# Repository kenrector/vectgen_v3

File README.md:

# vectgen_v3
kicad project for Wells-Gardner display controller

This is an ESP32 based interface to the Wells-Gardner 15v2000 BW X-Y display perhaps originally found
in the Atari Asteroids and Lunar Lander cocktail style arcade games.  The display is controlled by
X-Y voltages in the ranges +/- 0-10v and Z voltage 0-5v. 

The ESP32 processor is resident on a Wiretag WT32-ETH01 board and interfaces with client software via
the LAN connection.

Input commands from the client are move, draw, and zero, with related 12bit vector values sent to
X and Y MCP4922 DAC channels via the SPI interface.

Output from the DAC is translated to a bipolar voltage input to op amp integrator.  Integrator output is
input to the WG display.

Integrator input is switched by ADG201S CMOS switches controlled by the ESP32 software.  The integrators
are reset to zero by ADG201s switches also controlled by the ESP32.

A Z axis control to switch the CRT beam is provided by simple transistor logic.

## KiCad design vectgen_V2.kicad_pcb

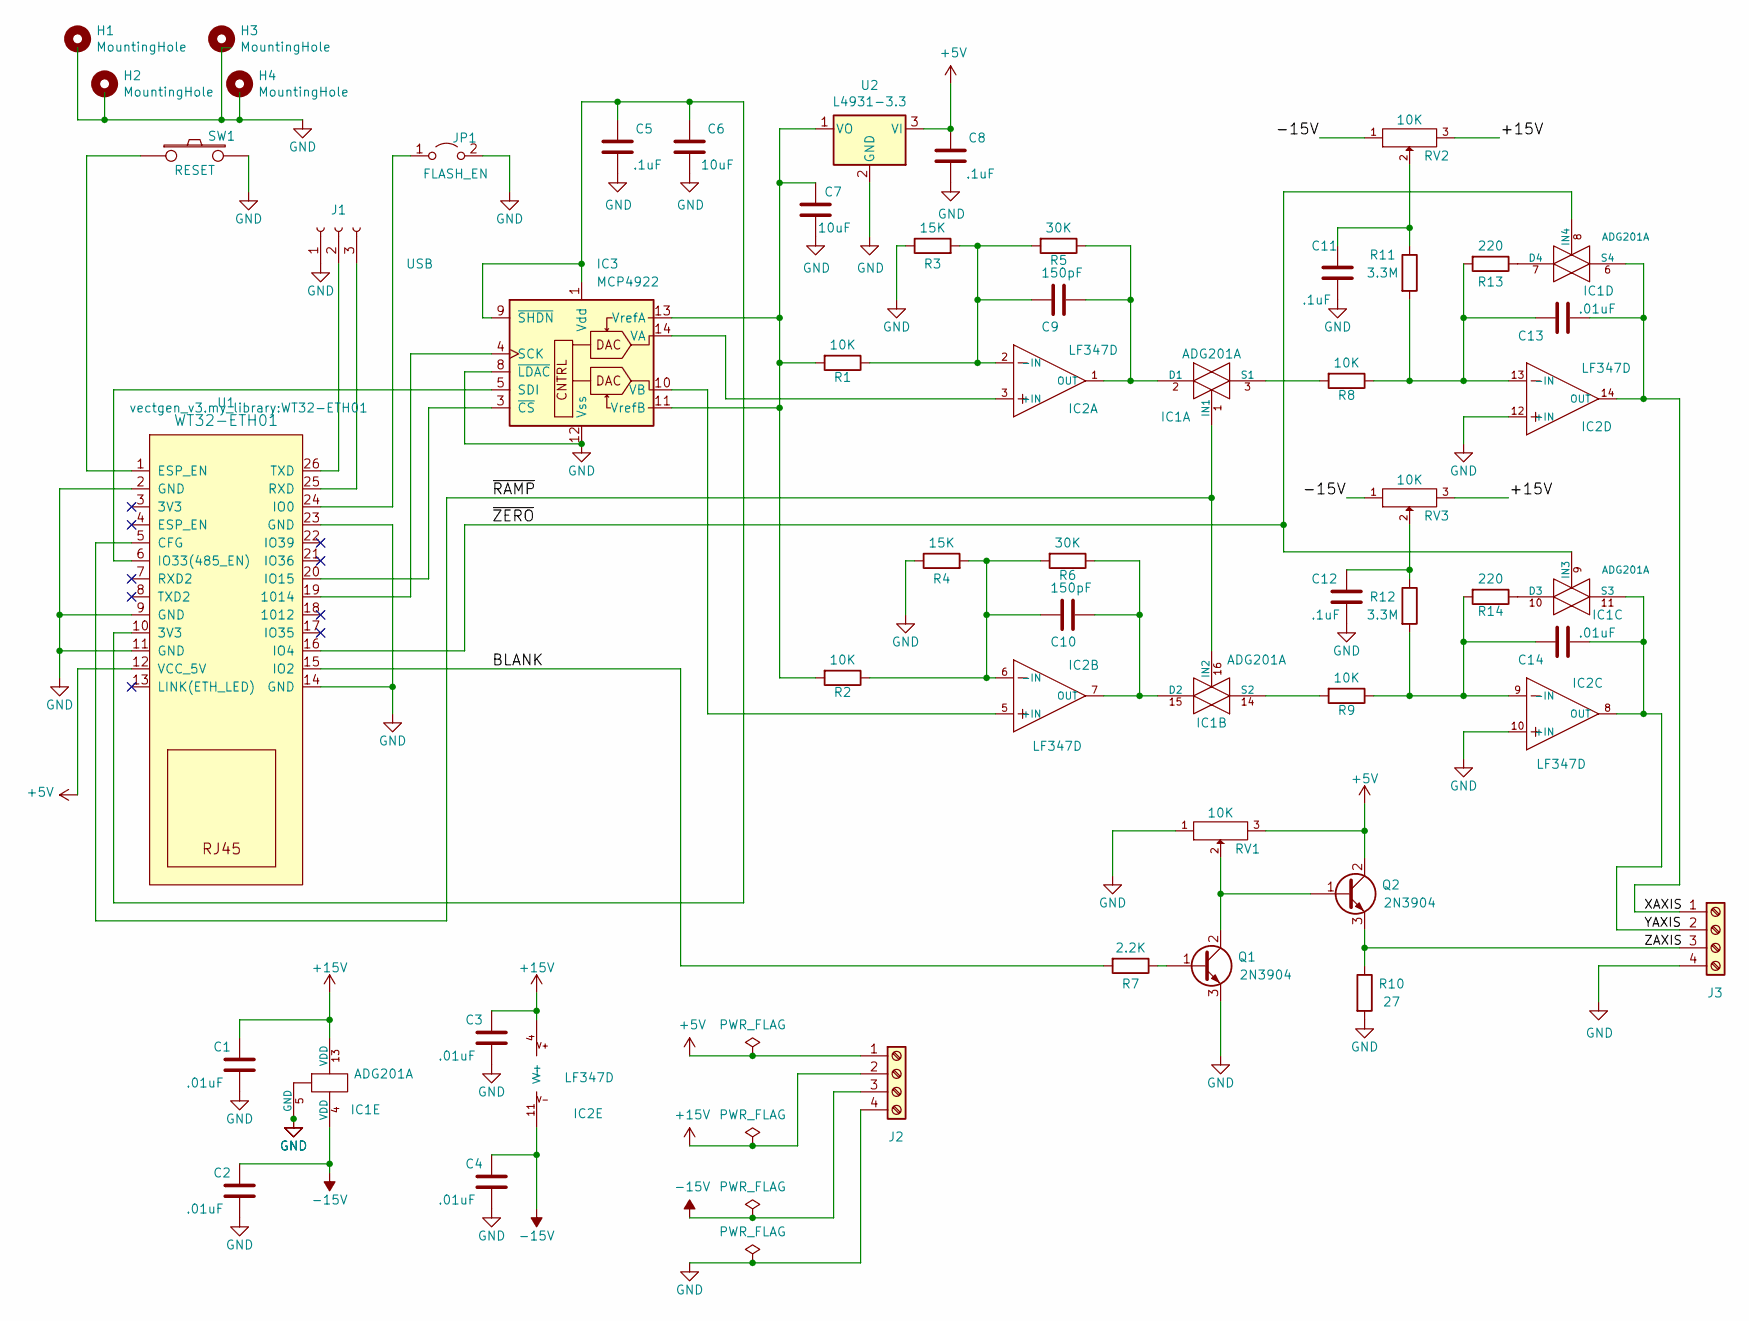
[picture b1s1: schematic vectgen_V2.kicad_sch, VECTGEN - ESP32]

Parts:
C1, C2, C3, C4: .01uF; C_Disc_D5.0mm_W2.5mm_P5.00mm
C5, C8, C11, C12: .1uF; C_Disc_D5.0mm_W2.5mm_P5.00mm
C6, C7: 10uF; C_Disc_D5.0mm_W2.5mm_P5.00mm
C9, C10: 150pF; C_Disc_D5.0mm_W2.5mm_P5.00mm
C13, C14: .01uF; C_Rect_L11.0mm_W2.8mm_P10.00mm_MKT
H1, H2, H3, H4: MountingHole; MountingHole_3.7mm_Pad_TopBottom
IC1: ADG201A; DIP-16_W7.62mm
IC2: LF347D; DIP-14_W7.62mm
IC3: MCP4922; DIP-14_W7.62mm
J1: USB; PinHeader_1x03_P2.54mm_Vertical
J2, J3: Screw_Terminal_01x04; TerminalBlock_bornier-4_P5.08mm
JP1: FLASH_EN; PinHeader_1x02_P2.54mm_Vertical
Q1, Q2: 2N3904; TO-92
R1, R2, R8, R9: 10K; R_Axial_DIN0204_L3.6mm_D1.6mm_P7.62mm_Horizontal
R3, R4: 15K; R_Axial_DIN0204_L3.6mm_D1.6mm_P7.62mm_Horizontal
R5, R6: 30K; R_Axial_DIN0204_L3.6mm_D1.6mm_P7.62mm_Horizontal
R7: 2.2K; R_Axial_DIN0204_L3.6mm_D1.6mm_P7.62mm_Horizontal
R10: 27; R_Axial_DIN0204_L3.6mm_D1.6mm_P7.62mm_Horizontal
R11, R12: 3.3M; R_Axial_DIN0204_L3.6mm_D1.6mm_P7.62mm_Horizontal
R13, R14: 220; R_Axial_DIN0204_L3.6mm_D1.6mm_P7.62mm_Horizontal
RV1, RV2, RV3: 10K; Potentiometer_Bourns_3296W_Vertical
SW1: RESET; PinHeader_1x02_P2.54mm_Vertical
U1: WT32-ETH01
U2: L4931-3.3; TO-92_Inline

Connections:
+5V: C8.2, J2.1, Q2.2 (C), RV1.3, U1.12 (VCC_5V), U2.3 (VI)
+15V: C1.1, C3.1, IC1.13 (VDD), IC2.4 (V+), J2.2, RV2.3, RV3.3
-15V: C2.1, C4.1, IC1.4 (VDD), IC2.11 (V-), J2.3, RV2.1, RV3.1
/BLANK: R7.2, U1.15 (IO2)
/XAXIS: C13.2, IC1.6 (S4), IC2.14 (OUT), J3.1
/YAXIS: C14.2, IC1.11 (S3), IC2.8 (OUT), J3.2
/ZAXIS: J3.3, Q2.3 (E), R10.1
/~RAMP: IC1.1 (IN1), IC1.16 (IN2), U1.5 (CFG)
/~ZERO: IC1.8 (IN4), IC1.9 (IN3), U1.16 (IO4)
GND: C1.2, C2.2, C3.2, C4.2, C5.1, C6.1, C7.1, C8.1, C11.2, C12.2, IC1.5 (GND), IC2.10 (+IN), IC2.12 (+IN), IC3.8 (~LDAC), IC3.12 (Vss), J1.1, J2.4, J3.4, JP1.2 (B), Q1.3 (E), R3.1, R4.1, R10.2, RV1.1, SW1.2, U1.2 (GND), U1.9 (GND), U1.11 (GND), U1.14 (GND), U1.23 (GND), U2.2 (GND)
unnamed: C5.2, C6.2, IC3.1 (Vdd), IC3.9 (~SHDN), U1.10 (3V3)
unnamed: C7.2, IC3.11 (VrefB), IC3.13 (VrefA), R1.2, R2.2, U2.1 (VO)
unnamed: C9.1, IC1.2 (D1), IC2.1 (OUT), R5.1
unnamed: C9.2, IC2.2 (-IN), R1.1, R3.2, R5.2
unnamed: C10.1, IC1.15 (D2), IC2.7 (OUT), R6.1
unnamed: C10.2, IC2.6 (-IN), R2.1, R4.2, R6.2
unnamed: C11.1, R11.1, RV2.2
unnamed: C12.1, R12.1, RV3.2
unnamed: C13.1, IC2.13 (-IN), R8.1, R11.2, R13.2
unnamed: C14.1, IC2.9 (-IN), R9.1, R12.2, R14.2
unnamed: IC1.3 (S1), R8.2
unnamed: IC1.7 (D4), R13.1
unnamed: IC1.10 (D3), R14.1
unnamed: IC1.14 (S2), R9.2
unnamed: IC2.3 (+IN), IC3.14 (VA)
unnamed: IC2.5 (+IN), IC3.10 (VB)
unnamed: IC3.3 (~CS), U1.20 (IO15)
unnamed: IC3.4 (SCK), U1.19 (1014)
unnamed: IC3.5 (SDI), U1.6 (IO33(485_EN))
unnamed: J1.2, U1.26 (TXD)
unnamed: J1.3, U1.25 (RXD)
unnamed: JP1.1 (A), U1.24 (IO0)
unnamed: Q1.1 (B), R7.1
unnamed: Q1.2 (C), Q2.1 (B), RV1.2
unnamed: SW1.1, U1.1 (ESP_EN)

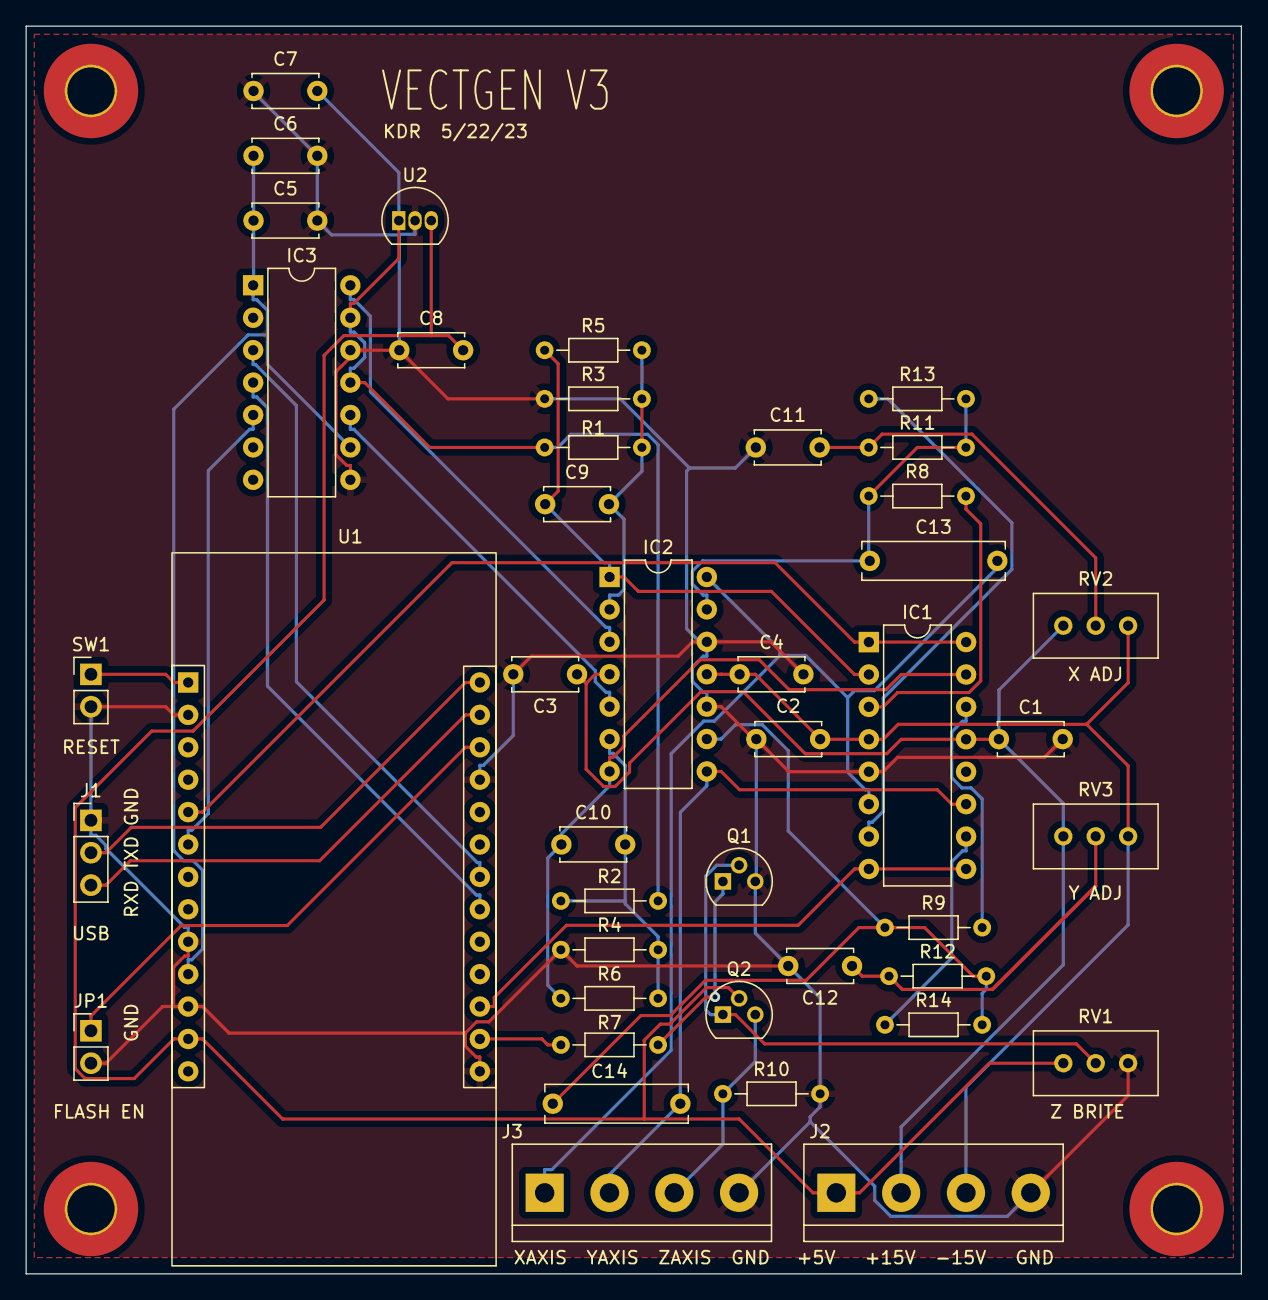
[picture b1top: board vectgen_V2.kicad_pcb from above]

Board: 2 copper layers, 95.2 x 97.8 mm, 47 parts (0 on the bottom side), 35 nets.

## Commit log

2022-04-10 add WT32-ETH01 schematic and WG manual
2023-05-27 updated files used to build PCB
